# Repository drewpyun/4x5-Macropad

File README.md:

# 4x5-Macropad
4x5 Macropad flashing guide 

First download:
QMK Toolkit: https://github.com/qmk/qmk_toolbox

QMK Toolkit will flash a .hex file to the PCB. 

# To get a hex file

We will use this website: https://kbfirmware.com/
Paste the following code into the text box and click "Import"
```
["Num Lock","/","*","-"],
["7\nHome","8\n↑","9\nPgUp","+"],
["4\n←","5","6\n→",{a:7},""],
[{a:4},"1\nEnd","2\n↓","3\nPgDn","Enter"],
["0\nIns",{a:7},"",{a:4},".\nDel",{a:7},""]
```
You should be greeted with something like this--

Click on the "Pins" Tab and change the controller to ATMEGA32**U2** and the Column 3 to **C7** like so.

Next, configure your keymaps on the keymap and macro tabs.
After you are finished, click on the compile tab, and save the file. 

Now open up QMK Toolbox and plug in your PCB. 
Change MCU to **atmega32u2**, and open the hex file under local file.

*If the pcb does not register on your computer you may need to hold down the reset switch located on the pcb.*

It should look something like this

Click flash.
Your PCB should disconnect and reconnect.

Test your pcb and everything should work!
Contact me at DrewGuy#0718 if you have problems.

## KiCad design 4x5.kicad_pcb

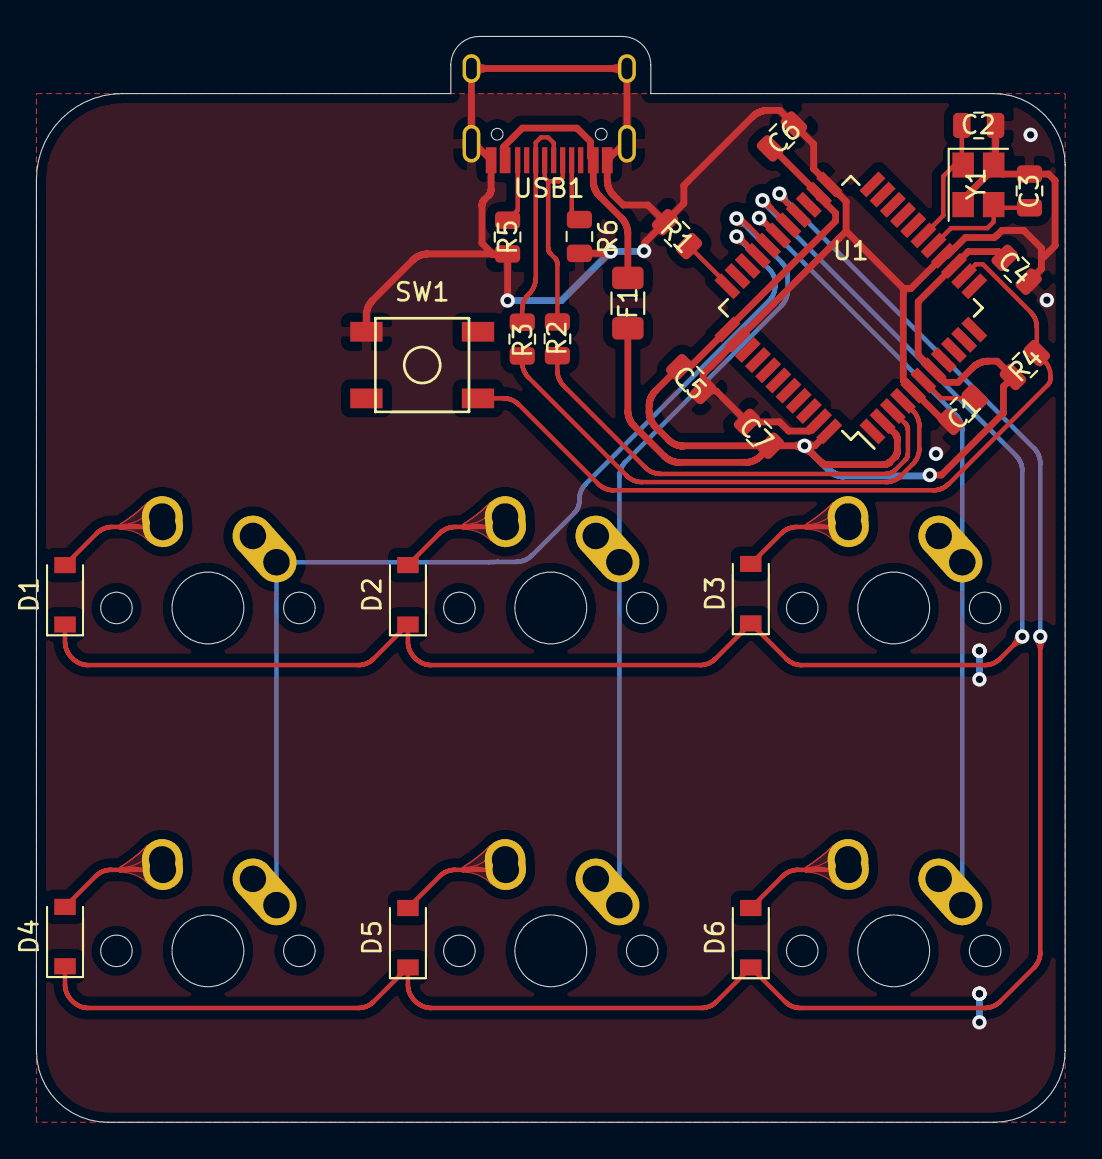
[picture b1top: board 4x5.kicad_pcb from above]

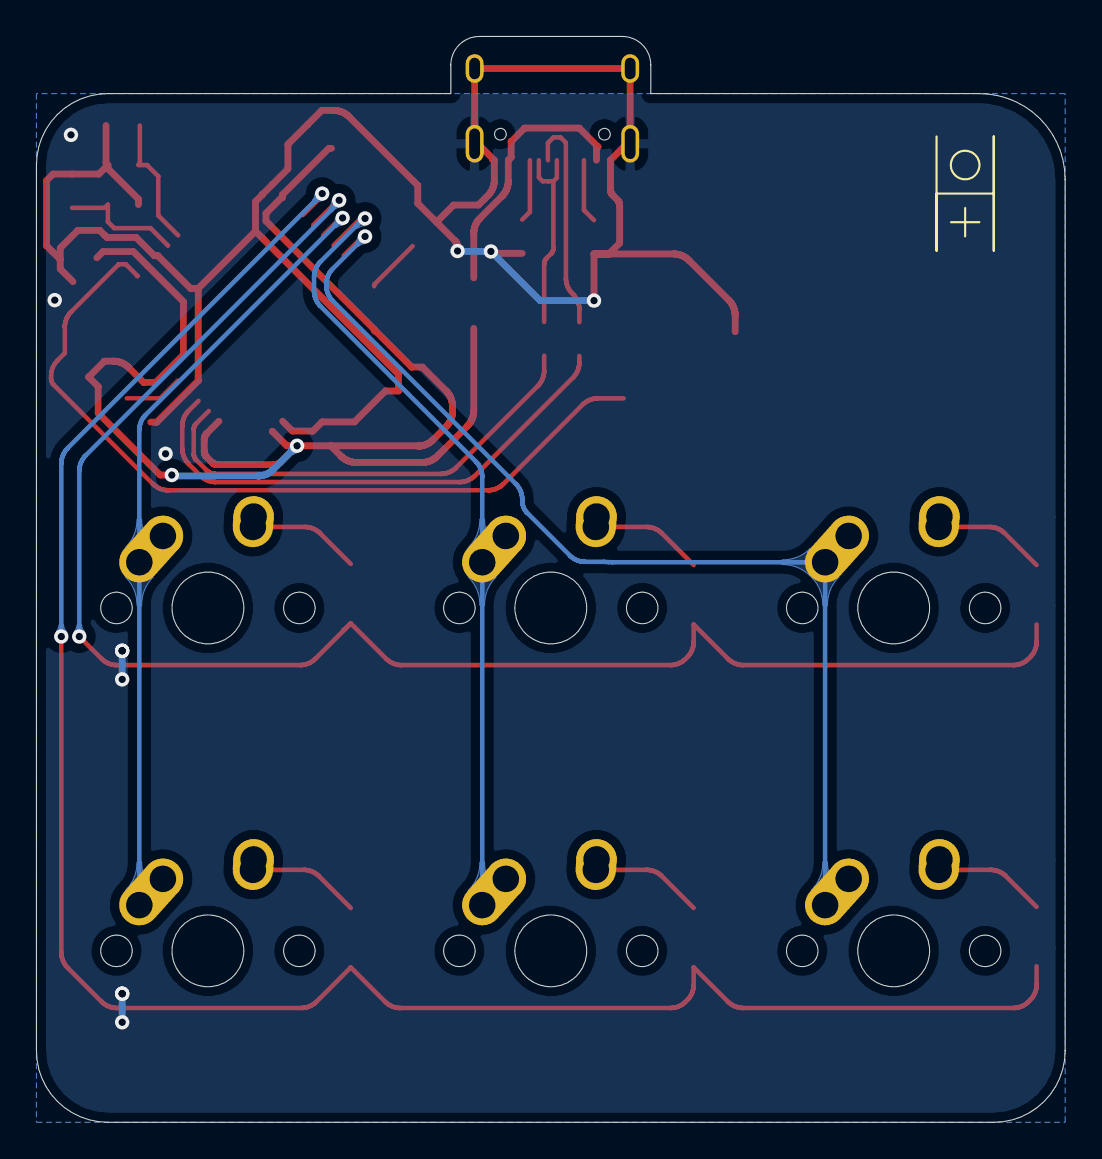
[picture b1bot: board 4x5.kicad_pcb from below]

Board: 2 copper layers, 57.1 x 60.3 mm, 30 parts (6 on the bottom side), 25 nets.

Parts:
C1: 1uF; C_0805_2012Metric
C2, C3: 22p; C_0805_2012Metric
C4, C5, C6: 0.1uF; C_0805_2012Metric
C7: 10uF; C_0805_2012Metric
D1, D2, D3, D4, D5, D6: D_Small; D_SOD-123
F1: 500mA; Fuse_1206_3216Metric
MX1, MX2, MX3, MX4, MX5, MX6: MX-NoLED; MX-1U-NoLED
R1, R4: 10k; R_0805_2012Metric
R2, R3: 22; R_0805_2012Metric
R5, R6: 5.1k; R_0805_2012Metric
SW1: SW_Push; SKQG-1155865
U1: ATmega32U4-AU; TQFP-44_10x10mm_P0.8mm
USB1: HRO-TYPE-C-31-M-12
Y1: 16MHz; Crystal_SMD_3225-4Pin_3.2x2.5mm

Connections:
+5V: C4.1, C5.1, C6.1, C7.1, F1.2, R4.2, U1.2, U1.7, U1.14, U1.24, U1.34, U1.44
D+: R3.2, USB1.6, USB1.8
D-: R2.2, USB1.5, USB1.7
GND: C1.2, C2.2, C3.2, C4.2, C5.2, C6.2, C7.2, R1.1, R5.1, R6.1, SW1.1, U1.5, U1.15, U1.23, U1.35, U1.43, USB1.1, USB1.12, USB1.13, Y1.2, Y1.4
unnamed: C1.1, U1.6
unnamed: C2.1, U1.17, Y1.1
unnamed: C3.1, U1.16, Y1.3
unnamed: D1.2, MX1.2
unnamed: D2.2, MX2.2
unnamed: D3.2, MX3.2
unnamed: D4.2, MX4.2
unnamed: D5.2, MX5.2
unnamed: D6.2, MX6.2
unnamed: R1.2, U1.33
unnamed: R2.1, U1.3
unnamed: R3.1, U1.4
unnamed: R4.1, SW1.2, U1.13
unnamed: R5.2, USB1.10
unnamed: R6.2, USB1.4
VCC: F1.1, USB1.2, USB1.11
col0: MX1.1, MX4.1, U1.30
col1: MX2.1, MX5.1, U1.29
col2: MX3.1, MX6.1, U1.28
row0: D1.1, D2.1, D3.1, U1.27
row1: D4.1, D5.1, D6.1, U1.26

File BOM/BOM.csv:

Comment,Designator,Footprint,LCSC
1uF,C1,Capacitor_SMD:C_0805_2012Metric,
0.1uF,"C4,C5,C6",Capacitor_SMD:C_0805_2012Metric,
10uF,"C2,C3,C7",Capacitor_SMD:C_0805_2012Metric,
D_Small,"D1,D2,D3,D4,D5,D6",Diode_SMD:D_SOD-123,
500mA,F1,Fuse:Fuse_1206_3216Metric,
MX-NoLED,"MX1,MX2,MX3,MX4,MX5,MX6",MX_Alps_Hybrid:MX-1U-NoLED,
10k,"R1,R4",Resistor_SMD:R_0805_2012Metric,
22,"R2,R3",Resistor_SMD:R_0805_2012Metric,
5.1k,"R5,R6",Resistor_SMD:R_0805_2012Metric,
SW_Push,SW1,random-keyboard-parts:SKQG-1155865,
ATmega32U4-AU,U1,Package_QFP:TQFP-44_10x10mm_P0.8mm,
HRO-TYPE-C-31-M-12,USB1,Type-C:HRO-TYPE-C-31-M-12,
16MHz,Y1,Crystal:Crystal_SMD_3225-4Pin_3.2x2.5mm,

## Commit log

2020-07-08 sub modules added
2020-07-08 sub library added to kicad
2020-07-08 update pcb and type c sub library
2020-07-08 finished schem
2020-07-11 finished pcb
2020-07-12 added BOM, CPL, GERBER
2020-10-24 final update
